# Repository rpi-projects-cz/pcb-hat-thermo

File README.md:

# Project pcb-hat-thermo

Goal of this project is to design Raspberry Pi Zero extension HAT to support DS18B20 senzor based thermometers that are using 1-wire protocol via GPIO 04.

Intended HAT needs to be stackable and compatible with other modules unless they are using GPIO 04 PIN.

The cirquit is using Pull-Up resistor R1 to deliver 3.3v voltage, generating logical 1 value on DATA pin. In order to generate logical 0 value, the temperature sensor will short the DATA pin to ground and deliver 0v voltage on DATA pin. Because direct wiring between DATA pin and 3.3v might damage Raspberry Pi, we are using resistore R1 10kΩ to reduce electrical current to acceptable value of 0.33 mA (maximum is 0.5 mA).

```text
Current (A) = Voltage (V) / Resistency (R) = 3.3V / 10000Ω = 0.00033 A = 0.33 mA
```

Reference architecture for this design is based on following article and associated cabling diagram.

- [Raspberry Pi DS18B20 Temperature Sensor Tutorial](https://www.circuitbasics.com/raspberry-pi-ds18b20-temperature-sensor-tutorial/)

This PCB is designed in [KiCad](https://www.kicad.org) 6.0.1-0.

## Logical Design

Following picture is capturing logical design.

There are five Phoenix Horizontal 1x03 P3.50mm connectors on the board, each with following connectivity:

- GND - Ground, connected to PIN 25
- 3.3v - VCC power 3.3v, connected to PIN 17
- DAT - Data, 1-wire protocol data connected to PIN 07 (GPIO 04)

Since the 1-wire protocol is addressable, all connectors are wired in chain, having Pull-Up resistor R1 10kΩ between DAT and 3.3v links.

Resistor R1 is 10kΩ SMD resistor with form factor [0805](https://en.wikipedia.org/wiki/List_of_integrated_circuit_packaging_types#Rectangular_passive_components).

## Physical Design

Pictures below are visualizing the final PCB as designed in KiCad.

Source files, including `kicad_pcb` are in the [KiCad/pcb-hat-thermo](KiCad/pcb-hat-thermo) directory.

## Contributing

This is open source project based on Eclipse public license. Any feedback, suggestions, correction or any other contributions are highly welcomed.

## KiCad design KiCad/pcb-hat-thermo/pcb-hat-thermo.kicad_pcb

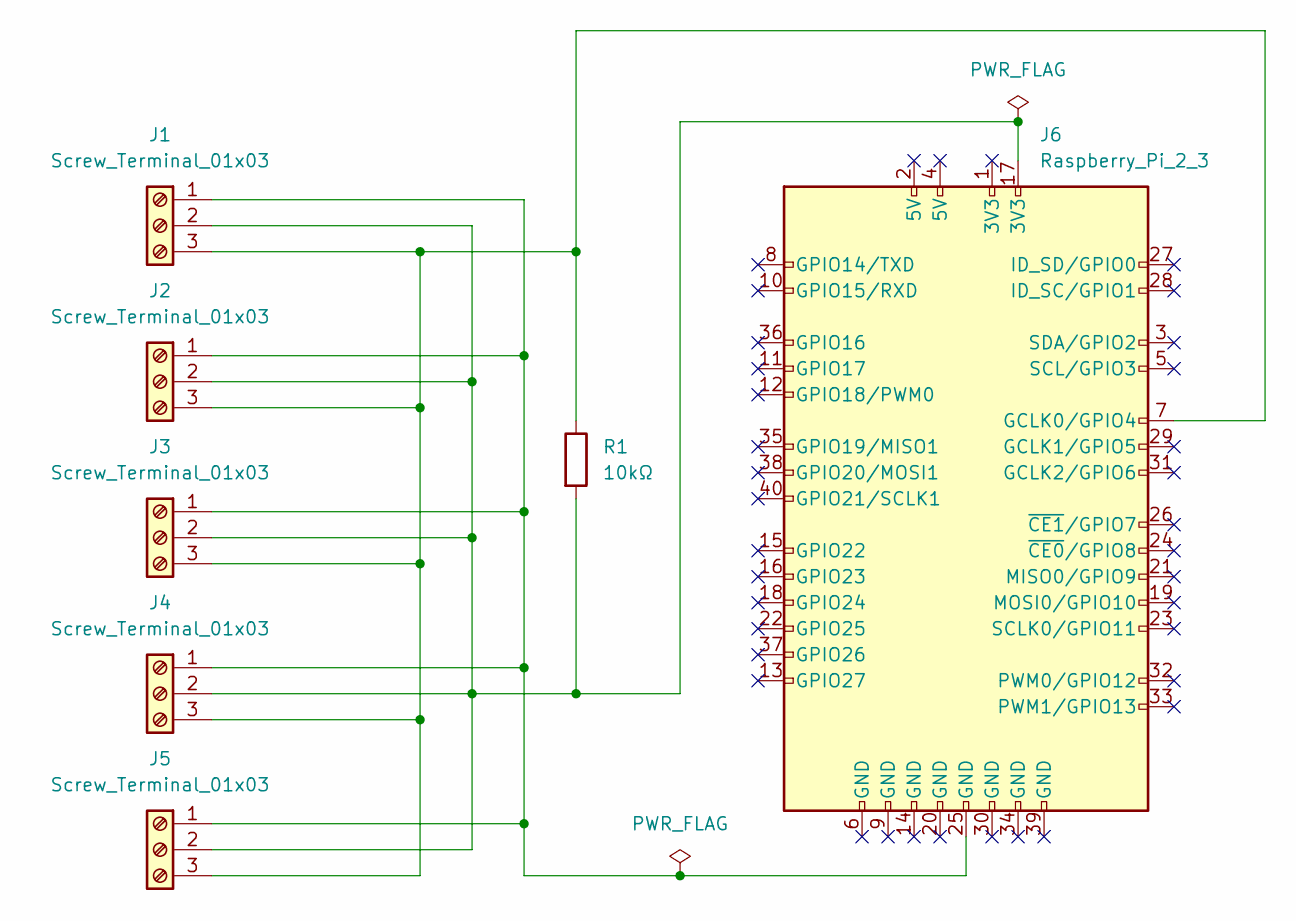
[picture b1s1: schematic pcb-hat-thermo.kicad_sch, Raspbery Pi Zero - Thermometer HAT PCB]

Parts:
J1, J2, J3, J4, J5: Screw_Terminal_01x03; PhoenixContact_MC_1,5_3-G-3.5_1x03_P3.50mm_Horizontal
J6: Raspberry_Pi_2_3; Raspberry_Pi_Zero_Custom_with_Header
R1: 10kΩ; R_0805_2012Metric

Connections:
unnamed: J1.1, J2.1, J3.1, J4.1, J5.1, J6.25 (GND)
unnamed: J1.2, J2.2, J3.2, J4.2, J5.2, J6.17 (3V3), R1.2
unnamed: J1.3, J2.3, J3.3, J4.3, J5.3, J6.7 (GCLK0/GPIO4), R1.1

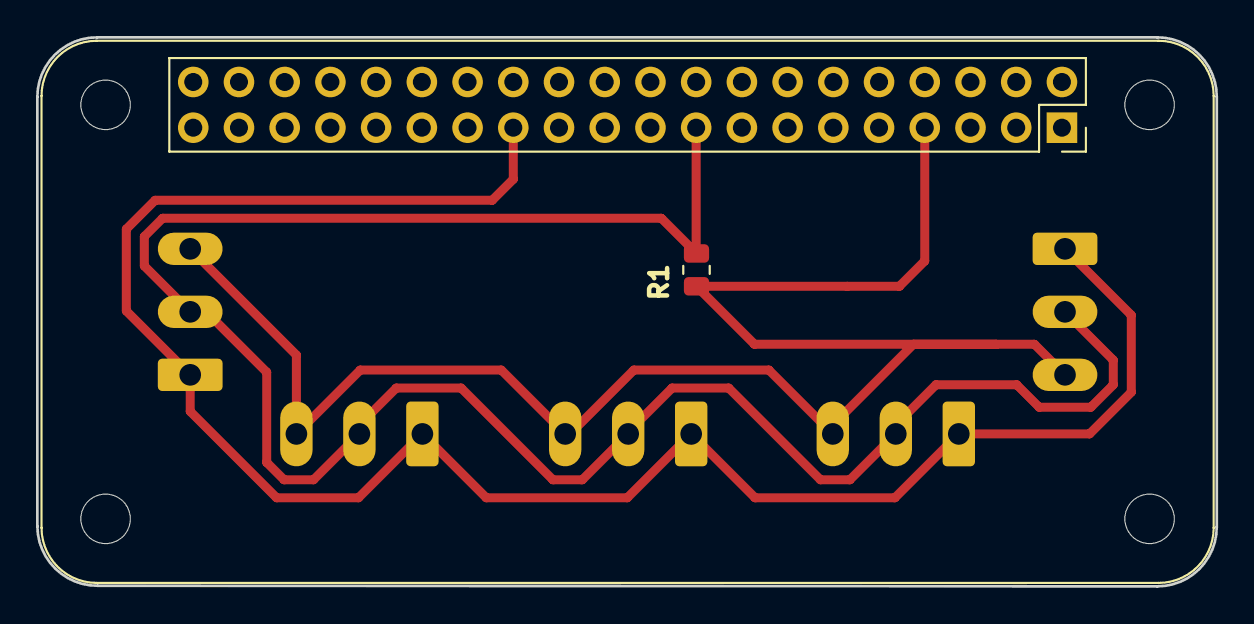
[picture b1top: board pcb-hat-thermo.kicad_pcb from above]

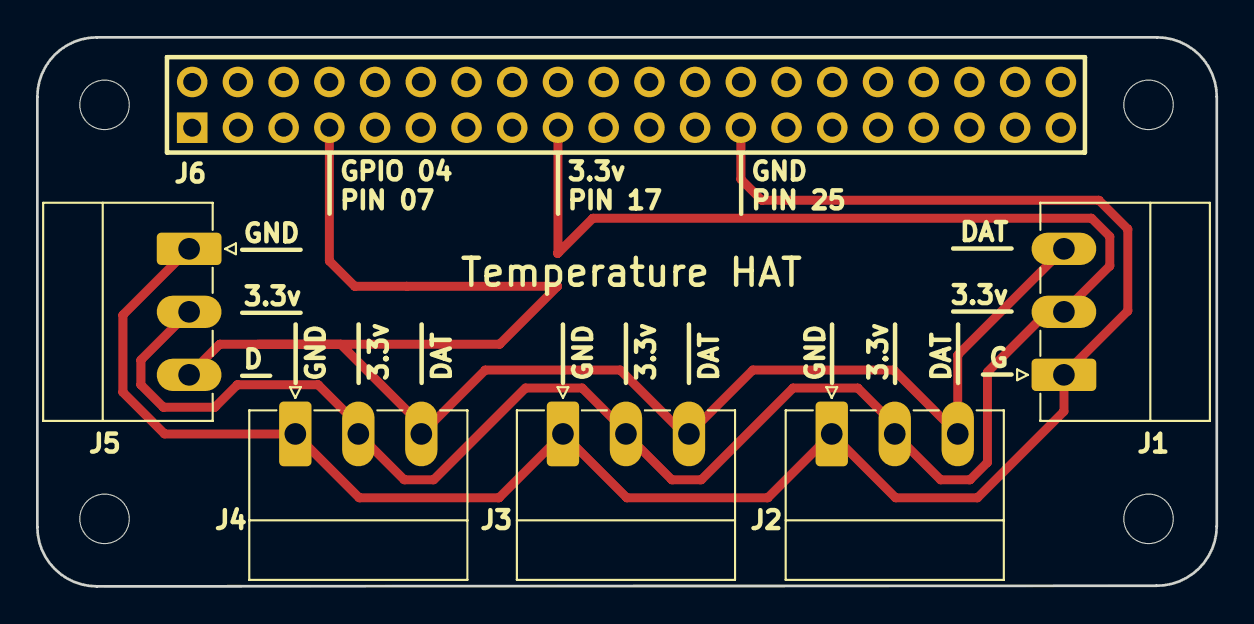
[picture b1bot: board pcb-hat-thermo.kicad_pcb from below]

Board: 2 copper layers, 65.5 x 30.5 mm, 7 parts (5 on the bottom side), 3 nets.

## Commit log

2022-02-14 Release 1
2022-02-14 Version 1.0
2022-02-14 Version 1.0
    * Initial commit
    * Release 1
    * Version 1.0
